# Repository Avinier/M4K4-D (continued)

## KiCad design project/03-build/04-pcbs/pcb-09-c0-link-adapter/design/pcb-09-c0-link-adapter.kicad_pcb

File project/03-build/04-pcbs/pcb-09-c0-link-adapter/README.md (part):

# PCB-09 — C0 link adapter

Pi-header board: 2 × RS-422 (THVD1451), audio pass-through and the enclosure-fan switch `J9-4`. **Rev A designed** ([D-092](../../decisions.md#d-092)): 77 × 22.7 × 1.6 mm, four layers, on the Pi header through a Samtec SSW-120-01-T-D socket and two M2.5 × 11 mm standoffs. **Rev B routed and CAD fitted on `pcb-09-revB`, not released** ([D-098](../../decisions.md#d-098)): 89 × 22.7 × 1.6 mm overall, adding the D-096 button/OFF and INA226 service interface. The #2813, Pi-image and populated bench gates below still apply; do not order either revision yet.

| | |
|---|---|
| Register | [04-pcbs board register](../README.md#board-register) |
| Project BOM | CH-084 in [BOM.csv](../../BOM.csv) |
| Location | Body, on the Pi header |
| Specification | [audiosystem.md §4](../../02-body/v1/research/audiosystem.md#4-audio-functions-on-the-shared-boards)<br>[D-042](../../decisions.md#d-042), [D-073](../../decisions.md#d-073), [D-074](../../decisions.md#d-074), [D-092](../../decisions.md#d-092), [D-098](../../decisions.md#d-098) |
| CAD placeholder | `_c0_link_adapter()` in [`body_v1_model.py`](../../02-body/v1/cad/body_v1_model.py) |
| CAD labels | `C0_LINK_ADAPTER_PCB09` |
| Final CAD | `Custom PCBs › PCB-09 C0 link adapter` in [makad-v1.step.py](../../final/v1/cad/makad-v1.step.py): rev-B KiCad STEP, standoffs, screws and five mated plugs ([pcb_integration.py](../../final/v1/cad/pcb_integration.py)); rev-B fit 8/8, mount 7/7 and integration PASS |

## Stages

See [workflow.md](../workflow.md) for what each stage involves and when it is done.

| Stage | Status | Revision / evidence | Date |
|---|---|---|---|
| 1. Design | **Rev B routed and CAD fitted; electrical release gates open** ([D-098](../../decisions.md#d-098)) | ERC 0; exported netlist audit PASS for 118 connected pins; Nightly DRC 0 violations / 0 unconnected / 0 parity; rev-B fit 8/8, mount 7/7, final integration PASS. `fab/revB` is a draft output, not an order release. | 2026-11-08 |
| 2. Procure | Waits for rev B and the design batch ([D-064](../../decisions.md#d-064)) | Do not order fab/revA | — |
| 3. Integrate | Rev B CAD replacement complete; physical acceptance open | [pcb_integration.py](../../final/v1/cad/pcb_integration.py), `check_pcb_integration.py`; J6 lead route to rear bay passes a 3 mm CAD reserve with 0.2 mm margin. J6 must be mated before tray installation. | 2026-11-08 |

### Rev B input — D-098

Preserve the rev A functions, socket, mounting and existing connector pinouts. Add accessible service access to **GPIO12 / header 32** for the qualified 0–3.3 V button-sense signal and **GPIO13 / header 33** for the M1 OFF command. The [D-098 amendment](../../decisions.md#d-098) assigns the INA226 to a local `i2c-gpio` bus: draft SDA on GPIO16 / header 36 and SCL on GPIO26 / header 37, plus Pi 3.3 V and GND. Physical pins 3/5 keep their rev A I²C1 routes to TP1/TP2 only. TP5 and TP1/TP2 are 1 mm probe pads, not harness terminations.

Rev B selects J6 as a top-entry GH6 on the +X extension. CAD checks its mated plug, a 3 mm lead corridor toward the rear buffer, and pre-mated tray insertion; add strain relief and pull-test the lead on the populated build. Keep the M1 ON pack-voltage node off this board: GPIO12 receives only the output of the measured high-impedance interface, with no back-power path into an unpowered Pi. Check GPIO13's inactive state through Pi reset, boot and halt, and any M1-to-GPIO13 injection with Pi power absent, before connecting OFF. ERC/DRC, six-net continuity/no-short checks and N1 are release gates. D-096's separate electrical HOLD still applies.

### Rev B routing study — 2026-11-08

The [rev B schematic](design/pcb-09-c0-link-adapter.kicad_sch) adds J6 (GH6: **1 3V3, 2 SDA, 3 SCL, 4 GND, 5 BTN_SENSE, 6 PWR_OFF**), R7 10 kΩ button pull-up to Pi 3V3, R8 2.2 kΩ button series, C5 100 nF optional/DNP, R9 1 kΩ OFF series, R10 100 kΩ OFF pull-down, and R11/R12 4.7 kΩ pull-ups for the software I²C bus. GPIO12/13 terminate at header pins 32/33; draft SDA/SCL terminate at pins 36/37. The connector nets are on the 3.3 V side; pack voltage and load current are absent. The received #2813 measurements still gate final values and buffer choice.

| Header pin | Rev B schematic net | Destination | Layout status |
|---|---|---|---|
| 3 / GPIO2 | I2C1_SDA | TP1 only, unchanged from rev A | Rev A route retained in rev B |
| 5 / GPIO3 | I2C1_SCL | TP2 only, unchanged from rev A | Rev A route retained in rev B |
| 32 / GPIO12 | BTN_GPIO12 | R8 → BTN_SENSE at J6.5 | Routed in rev B; DRC 0/0/0 |
| 33 / GPIO13 | OFF_GPIO13 | R9 → PWR_OFF at J6.6 | Routed in rev B; DRC 0/0/0 |
| 36 / GPIO16 | I2C_GPIO_SDA | R11 pull-up and J6.2 | Routed in rev B; DRC 0/0/0 |
| 37 / GPIO26 | I2C_GPIO_SCL | R12 pull-up and J6.3 | Routed in rev B; DRC 0/0/0 |

The draft rev B allocation has **15 functional GPIO** (rev A's 11 plus GPIO12/13/16/26) and keeps GPIO2/3 reserved for I²C1 service pads. Layout and CAD fit validate GPIO16/26 and a top-entry GH6 at the +X extension; electrical acceptance is pending.

An exploratory GH6 placement needed an extension at the bay's +X edge: the existing F.Cu courtyards occupy the top of the original bay. A geometric core-only probe of world X 66…78, Y 22.5…39, Z 106.25…108.25 found no intersecting robot solid. That probe did **not** validate the mated plug, cable exit, insertion sweep, mount or full board. Growing the +Y edge instead intersected the existing J9-1 mated plug and its reserve.

The manually routed exploratory I²C1 board failed Nightly DRC: **29 violations, 2 unconnected and 0 parity** ([study report](design/revB-routing-study-drc.json)). The SDA F.Cu L path crossed LRCLK near header pin 35; the proposed layer change landed on the existing 5 V via. The SCL B.Cu U path crossed BASE_TX and approached a ground socket pad. The GPIO12/13 In1 paths isolated ground socket pads 30/34; J6's +X placement also conflicted with nearby vias. D-098 therefore switches the INA226 to local GPIO I²C and forbids new In1 tracks. This report is historical evidence from the rejected route.

The amended rev B layout uses local rev A escape reroutes near header pins 32–38, preserves every rev A net and connector pinout, adds no signal track to In1, and passes Nightly DRC 0/0/0. The +X extension ends at world X 78 and steps its +Y edge back to Y 38.9 to clear the body frame. The rev B STEP passes `check_pcb09_fit.py` 8/8, `check_pcb09_mount.py` 7/7, and `check_pcb_integration.py` PASS. `fab/revB/` was exported only after that CAD fit and remains a draft until the bench gates close.

Current evidence: [DRC/parity](design/layout-drc.json), [rev B board STEP](cad/pcb-09-c0-link-adapter-revB.step), [fit report](../../final/v1/cad/check_pcb09_fit-revB-report.json), [mount report](../../final/v1/cad/check_pcb09_mount-revB-report.json), [final STEP integration report](../../final/v1/cad/pcb-integration-report.json), and [draft fabrication outputs](fab/revB/README.md). C5 is DNP and omitted from the assembly BOM/CPL. J6's plug must be mated before the tray slide; its 3 mm lead reserve clears to the rear buffer volume with 0.2 mm CAD margin.

## Inputs

Header audit started 2026-10-31. The electrical interface below is the **builder-agreed allocation baseline v0.2** ([D-073](../../decisions.md#d-073)); CR-02 and boot-safe audit closure remain open. The D-074 strip outline and all 40 socket pad positions have since been checked, and a review schematic and placement exist below. Socket selection, installed height, retention and populated fit were the remaining lesson-1 gaps; they are closed in the [input freeze](#input-freeze--2026-11-06-d-092) (D-092).

**Audio contract, inherited from PCB-05.** `J9-3` (audio, `W26` to the BO-067 audio hub) carries signals only: GPIO18 BCLK, GPIO19 LRCLK, GPIO20 SDI0, GPIO22 SDI1, GPIO21 SDO0, GPIO23 `AMP_SD`, the Pi's 3V3, two GND and one spare, and **no 5 V** ([D-067](../../decisions.md#d-067), PCB-05 2026-10-27; `CA-06` CR-01 accepted there). The retained pin order is **1 3V3, 2 LRCLK, 3 GND, 4 BCLK, 5 GND, 6 SDO0, 7 SDI1, 8 SDI0, 9 AMP_SD, 10 spare (5V_SENSE)**; W26 is wired 1:1 to the hub. The spare still reaches only an isolated test pad on PCB-09; the retired PCB-05 divider is not fitted or part of the current build.

**Set by other boards.** `J9-2` (base link, `W25` to PCB-10 `J10-2`) was set by [PCB-10](../pcb-10-c3-carrier/README.md#connectors-and-who-owns-each-pin-order) on 2026-10-27 and reordered at its layout on 2026-10-28 (the order its THVD1451's pins come in, so the pairs run straight). The pairs are named by direction so `W25` is wired 1:1: 1 GND, 2 `C0TX+` and 3 `C0TX−` (this board's driver `Y`/`Z`), 4 `C3TX−` and 5 `C3TX+` (this board's receiver `B`/`A`, with its 120 Ω termination), 6 spare. The `J9-1` head link may follow the same rule; that is this board's choice.

### Pi 5 header audit — 2026-10-31

**Lesson.** A GPIO has three separate properties: where it is on the connector, which peripheral it can carry, and what voltage it presents before software takes control. A correct UART pin can still send a break at boot; a correct fan pin can still turn the switch partly on if its bias is wrong. Covering all 40 contacts also makes PCB-09 responsible for access to reserved buses. Mechanical contact with a socket does not imply an electrical trace on the adapter.

**Result:** BCM-to-header mappings and proposed peripheral functions pass the paper check; the active owners do not overlap. **The complete boot-safe interface is not yet passed or frozen. CR-02 remains OPEN:** GPIO24 is the builder-selected, conflict-free fan pin; accepting the entire change still requires the outstanding evidence below. CR-01 remains accepted under D-067; this audit adds software implementation conditions rather than reopening that allocation. The builder accepted HA-02…04's recommended dispositions on 2026-10-31 (D-073), explicitly retaining CR-02 as open.

#### Evidence and authority

Read on 2026-10-31. RP-02 is read-only; build changes belong here and in [decisions.md](../../decisions.md); the selected dispositions are recorded as D-073. Source-code URLs use Raspberry Pi's `rpi-6.12.y` branch as an inspected reference, **not** evidence of the kernel installed on C0.

| Ref | Source | What was checked |
|---|---|---|
| H | Raspberry Pi [40-pin header documentation](https://www.raspberrypi.com/documentation/computers/raspberry-pi.html#gpio) and its [pin diagram](https://raw.githubusercontent.com/raspberrypi/documentation/master/documentation/asciidoc/computers/raspberry-pi/images/GPIO-Pinout-Diagram-2.png) | All 40 physical positions, supply contacts, GPIO0/1 reservation; 3.3 V GPIO, no 5 V tolerance. The shared diagram's older peripheral labels are not the Pi 5 mux authority |
| R | [RP1 peripherals datasheet](https://datasheets.raspberrypi.com/rp1/rp1-peripherals.pdf), §3.1 Table 4, GPIO CTRL and PADS Table 21 | UART/I²S mux, NULL reset function, output disabled and input buffer disabled at reset |
| P | Raspberry Pi engineer clarification, [Pi5 GPIO Reset Defaults](https://forums.raspberrypi.com/viewtopic.php?t=366826), 2024-03-04…06 | GPIO0–8 pull up; GPIO9–27 pull down. Table 21 only says “varies”; this clarification supplies the per-pin bias and corrects the initial “inputs” description |
| T | TI [THVD1451, SLLSEY3E](https://www.ti.com/lit/ds/symlink/thvd1451.pdf), §§7.3, 7.5, 7.7, 9.1 | 3.0–5.5 V operation, logic thresholds, receiver swing, 3 mA maximum no-load current; always-enabled driver and receiver |
| U | Official [uart0-pi5](https://raw.githubusercontent.com/raspberrypi/linux/rpi-6.12.y/arch/arm/boot/dts/overlays/uart0-pi5-overlay.dts), [uart2-pi5](https://raw.githubusercontent.com/raspberrypi/linux/rpi-6.12.y/arch/arm/boot/dts/overlays/uart2-pi5-overlay.dts), [rp1.dtsi](https://raw.githubusercontent.com/raspberrypi/linux/rpi-6.12.y/arch/arm64/boot/dts/broadcom/rp1.dtsi) and [overlay reference](https://raw.githubusercontent.com/raspberrypi/linux/rpi-6.12.y/arch/arm/boot/dts/overlays/README) | UART pin groups and optional flow-control claims; default I²S group stops at GPIO21 |
| F | Official [gpio-fan overlay](https://raw.githubusercontent.com/raspberrypi/linux/rpi-6.12.y/arch/arm/boot/dts/overlays/gpio-fan-overlay.dts) and [driver](https://raw.githubusercontent.com/raspberrypi/linux/rpi-6.12.y/drivers/hwmon/gpio-fan.c) | One active-high control pin; temperature and hysteresis parameters; probe preserves the observed GPIO level, shutdown drives off |
| B | Official [UART configuration](https://www.raspberrypi.com/documentation/computers/configuration.html#configuring-uarts) and [BOOT_UART](https://www.raspberrypi.com/documentation/computers/raspberry-pi.html#BOOT_UART) | Pi 5 debug UART is normally UART10 on the separate debug connector; configuration can change the primary UART, so silence on GPIO14 must be checked on the installed image |
| C | RP-02 [CA-06](../../../02-prototypes/RP-02-electrical/compute-control-architecture.md#ca-06--pi-gpio-allocation-reserves-independent-transports), [D-042](../../decisions.md#d-042), [D-043](../../decisions.md#d-043), [D-067](../../decisions.md#d-067), PCB-05/PCB-10 READMEs linked above | Existing allocations, fan circuit, selected 3010 fan, connector contracts and audio power ownership |

#### 40-row header interface (rev A baseline with rev B service additions)

Directions are relative to the Pi. `N↑`/`N↓` mean **NULL function, output disabled, input buffer disabled**, with the indicated weak pull at RP1 reset (R/P); they do not promise an unchanged state throughout firmware, Linux or a warm reboot. Voltages are nominal signal/rail domains, not absolute maximum ratings. `NC` means a socket contact with **no trace, via, test pad or other load on PCB-09**, apart from its own land. Reserved contacts remain reserved even when NC. Supply rows are shared rail contacts, not competing GPIO owners.

| Physical pin | BCM GPIO | PCB-09 net / disposition | Owner / authority | Direction | RP1 reset / external bias | Voltage |
|---|---|---|---|---|---|---|
| 1 | — | +3V3_PI | Pi supply → PCB-09 + audio hub | Power in | Rail sequencing | 3.3 V |
| 2 | — | +5V_PI → fan only | D-042 / D-043 | Power in | May remain powered at halt | 5 V |
| 3 | 2 | I2C1_SDA → labelled SDA service pad | CA-06 / D-073 housekeeping | Bidirectional | N↑; Pi has fixed pull-up | 3.3 V |
| 4 | — | +5V_PI, same rail as pin 2 | D-042 / D-043 | Power in | May remain powered at halt | 5 V |
| 5 | 3 | I2C1_SCL → labelled SCL service pad | CA-06 / D-073 housekeeping | Bidirectional | N↑; Pi has fixed pull-up | 3.3 V |
| 6 | — | GND | Common return | Return | GND | 0 V |
| 7 | 4 | BASE_TX → base THVD1451 D | CA-06 UART2 | Out | N↑; 4.7 kΩ to 3V3 (D-073) | 3.3 V |
| 8 | 14 | HEAD_TX → head THVD1451 D | CA-06 UART0 | Out | N↓; 4.7 kΩ to 3V3 (D-073) | 3.3 V |
| 9 | — | GND | Common return | Return | GND | 0 V |
| 10 | 15 | HEAD_RX ← head THVD1451 R | CA-06 UART0 | In | N↓; R drives after VCC valid | 3.3 V |
| 11 | 17 | NC; UART0 RTS prohibited | PCB-09 unused | — | N↓ | 3.3 V |
| 12 | 18 | BCLK → J9-3.4 | CA-06 / D-067 I²S0 | Out | N↓ | 3.3 V |
| 13 | 27 | NC | PCB-09 unused | — | N↓ | 3.3 V |
| 14 | — | GND | Common return | Return | GND | 0 V |
| 15 | 22 | SDI1 ← J9-3.7 | CR-01 / D-067 I²S0 | In | N↓; converter powered by Pi | 3.3 V |
| 16 | 23 | AMP_SD → J9-3.9 | CR-01 / D-067 GPIO | Out | N↓; verify amp/hub bias on the build | 3.3 V |
| 17 | — | +3V3_PI, same rail as pin 1 | Pi supply → PCB-09 + audio hub | Power in | Rail sequencing | 3.3 V |
| 18 | 24 | FAN_EN → 100 Ω → MOSFET gate | D-042 / D-073; CR-02 open | Out | N↓; 100 kΩ gate–source | 3.3 V |
| 19 | 10 | NC; SPI0 MOSI reserved | CA-06 SPI/service | — | N↓ | 3.3 V |
| 20 | — | GND | Common return | Return | GND | 0 V |
| 21 | 9 | NC; SPI0 MISO reserved | CA-06 SPI/service | — | N↓ | 3.3 V |
| 22 | 25 | NC | PCB-09 unused | — | N↓ | 3.3 V |
| 23 | 11 | NC; SPI0 SCLK reserved | CA-06 SPI/service | — | N↓ | 3.3 V |
| 24 | 8 | NC; SPI0 CE0 reserved | CA-06 SPI/service | — | N↑ | 3.3 V |
| 25 | — | GND | Common return | Return | GND | 0 V |
| 26 | 7 | NC; SPI0 CE1 / UART2 RTS alternatives | PCB-09 unused | — | N↑ | 3.3 V |
| 27 | 0 | NC; ID_SD only | Pi HAT-ID reservation | — | N↑ | 3.3 V |
| 28 | 1 | NC; ID_SC only | Pi HAT-ID reservation | — | N↑ | 3.3 V |
| 29 | 5 | BASE_RX ← base THVD1451 R | CA-06 UART2 | In | N↑; R drives after VCC valid | 3.3 V |
| 30 | — | GND | Common return | Return | GND | 0 V |
| 31 | 6 | NC; UART2 CTS prohibited | PCB-09 unused | — | N↑ | 3.3 V |
| 32 | 12 | BTN_GPIO12 via R8 from J6.5 BTN_SENSE | D-098 button sense | In | N↓; R7 pulls sense to Pi 3V3 | 3.3 V |
| 33 | 13 | OFF_GPIO13 via R9 to J6.6 PWR_OFF | D-098 M1 OFF | Out | N↓; R10 pulls PWR_OFF low | 3.3 V |
| 34 | — | GND | Common return | Return | GND | 0 V |
| 35 | 19 | LRCLK → J9-3.2 | CA-06 / D-067 I²S0 | Out | N↓ | 3.3 V |
| 36 | 16 | I2C_GPIO_SDA → J6.2; R11 pull-up | D-098 software I²C; UART0 CTS prohibited | Bidirectional | N↓; 4.7 kΩ to Pi 3V3 | 3.3 V |
| 37 | 26 | I2C_GPIO_SCL → J6.3; R12 pull-up | D-098 software I²C | Bidirectional | N↓; 4.7 kΩ to Pi 3V3 | 3.3 V |
| 38 | 20 | SDI0 ← J9-3.8 | CA-06 / D-067 I²S0 | In | N↓; converter powered by Pi | 3.3 V |
| 39 | — | GND | Common return | Return | GND | 0 V |
| 40 | 21 | SDO0 → J9-3.6 | CA-06 / D-067 I²S0 | Out | N↓ | 3.3 V |

**Rev B count:** 15 functional GPIO (including FAN_EN with CR-02 open), 2 reserved I²C1 GPIO exposed only on service pads, 11 other GPIO contacts, 4 supply contacts and 8 grounds = 40. GPIO0/1 have no adapter EEPROM or test points. Both contacts of each supply rail join that rail; all eight grounds join the common plane. J9-3.1 gets +3V3_PI; J9-3.3/.5 get GND. J9-3.10 goes **only to an isolated 5V_SENSE test pad**, never to a Pi GPIO or either supply. Its name does not make it a 5 V power connection.

#### Function selection and software ownership

Table 4 (R) confirms UART0 on GPIO14/15 at **a4**, UART2 on GPIO4/5 at **a2**, and I²S0 BCLK/WS/SDI0/SDO0/SDI1 on GPIO18/19/20/21/22 at **a2**. GPIO23 and GPIO24 use plain GPIO outputs (RIO path), never I²S. GPIO23's a2 is SDO1; GPIO24's a2 is SDI2, so enabling additional audio lanes indiscriminately would collide with both control signals.

| Consumer | Allowed GPIO claim | Condition / finding |
|---|---|---|
| `uart0-pi5` | 14, 15 | Use the Pi 5 overlay explicitly. No `ctsrts` or `rs485`: those also claim 16/17. Full-duplex THVD1451 needs no RTS control |
| `uart2-pi5` | 4, 5 | No `ctsrts` or `rs485`: those also claim 6/7 |
| Audio sound-card overlay | 18, 19, 20, 21, 22 only | **Not yet supplied or compiled.** The inspected `rp1_i2s0_18_21` group omits SDI1. Define/select a five-pin I²S0 group; keep GPIO23/24 out of it. Bind one shared clock interface with four capture channels on two stereo lanes and two-channel playback; enabling `i2s` alone is not a sound-card implementation |
| Amp control | 23 only | Start low; assert only after valid playback clocks/data; lower before stopping clocks and at orderly shutdown. One software owner; do not combine a permanent GPIO hog with a driver that also requests it |
| `gpio-fan` | 24 only | Proposed `dtoverlay=gpio-fan,gpiopin=24,temp=60000,hyst=5000`: 60 °C on / 55 °C off. Explicit pin required: the default is GPIO12. Temperatures remain bench starting points |
| I²C1 | 2, 3 reserved; SDA/SCL/GND service pads (D-073) | No additional pull-ups, attached consumer or bus cable. Keep the controller disabled until a consumer is deliberately configured |
| Button sense and M1 OFF (rev B) | 12 input, 13 output (D-098) | Button sense must be 0–3.3 V after a qualified rear buffer; verify GPIO13 stays inactive through boot, reboot and halt. J6 termination and cable CAD fit pass; electrical checks remain |
| `i2c-gpio` INA226 (rev B) | 16 SDA, 26 SCL | R11/R12 pull each line to Pi 3V3; keep UART0 flow control off and test INA226 at 0x40 on the actual Pi image |
| SPI0 | None | Reservation preserved; no adapter traces or access. SPI0's usual second CS is GPIO7, outside CA-06's 8–11 shorthand; leave SPI disabled unless deliberately configured |

**Console check is a release condition.** Pi 5 normally sends debug output through UART10, not GPIO14/15 (B); that is not proof that every EEPROM/image configuration is silent. Require EEPROM `BOOT_UART=0`, disable firmware debug output (`uart_2ndstage`), remove any kernel `console=`/`earlycon` targeting either link (including aliases), and disable serial getty/debug applications on both resolved ports. Preserve CA-06's stable udev names and boot mux self-test. Capture the installed EEPROM settings, `config.txt`, `cmdline.txt`, resolved aliases and enabled services; scope HEAD_TX through cold boot, warm reboot and shutdown. `enable_uart=1` alone is not the pin-ownership proof.

#### Boot/reset findings and selected circuit remedies

1. **FAN_EN: correct default, incorrect “beats any pull-up” premise.** GPIO24 is reset NULL/pulled down, so its internal pull and D-042's 100 kΩ gate-to-source resistor agree. Retain the 100 Ω series resistor, gate pull-down at the MOSFET, common source ground, flyback Schottky (cathode to FAN+, anode to FAN−), and local 10 µF + high-frequency bypass. A 100 kΩ pull-down does not dominate a tens-of-kΩ pull-up: even an illustrative 50 kΩ pull-up gives about 2.2 V at the gate. Thus no overlay/firmware may enable a pull-up or other function on GPIO24. With only 100 kΩ present, require the selected MOSFET's worst-case gate leakage plus board leakage to keep VGS below its off limit. Confirm gate voltage and fan inactivity on real cold boot/reset; an output driven high by a hung kernel is not corrected by a pull-down. This is a reset-off switch, not an independent thermal failsafe.
2. **UART TX: head reset is a break, not an unspecified floating signal.** GPIO14 defaults pulled down; THVD1451 forwards D continuously. GPIO4 defaults pulled up and is nominally idle-high. Add **4.7 kΩ from each D/TX to the same Pi 3V3 rail** (D-073): both links then have a deliberate idle-high bias before the UART owns them. TI specifies up to 6.2 µA D input leakage; include it and the opposing RP1 pull in the high-level calculation, against TI's 2.0 V VIH. A 100 kΩ pull-up is unsuitable against the head pin's pull-down. As a cross-check only, the [CM5 RP1 GPIO table](https://pip-assets.raspberrypi.com/categories/944-raspberry-pi-compute-module-5/documents/RP-008180-DS-7-cm5-datasheet.pdf?disposition=inline) gives a 35 kΩ minimum pull-down: 3.0 V × 35/(35+4.747) − 6.2 µA × (35 kΩ ∥ 4.747 kΩ) ≈ **2.62 V** with a +1% pull-up. This is a same-controller comparison, not a Pi 5 board-specific guaranteed limit; confirm the Pi 5 bound or measure with margin before sign-off. Low-state pull-up load at 3.3 V is about 0.70 mA. Pull-ups cannot suppress actively transmitted boot text or guarantee clean signalling while VCC ramps. C2/C3 must reject framing errors, breaks, stale sessions and invalid commands before arming; verify recovery after these events.
3. **AMP_SD: reset bias agrees with off.** GPIO23's pull-down reinforces PCB-05's external 100 kΩ and MAX98357A's internal pull-down, through the existing 2.2 kΩ series resistor (D-067). No I²S group may take GPIO23. That remote pull-down defines off if W26 is unplugged. PCB-05 owns the unpowered-amp SD_MODE injection mitigation; its accepted 2.2 kΩ circuit remains the contract. A warm reboot need not instantly restore RP1 reset defaults: test amp mute ordering rather than assuming it.
4. **Audio inputs and outputs.** SDI0/SDI1 come from converters supplied from the Pi's own 3V3, with a passive filtered mic rail; no independent 5 V receiver drives a Pi input. BCLK/LRCLK/SDO0 are outputs, normally held low by reset bias while the amp is off. Retain PCB-05's clock damping and verify clock edges and rail sequencing with the real W26. Shared supply origin does not by itself prove transient sequencing during a fast shutdown; scope the filtered rail and SDI lines at bring-up.

#### Voltage and rail budget

Both THVD1451 VCC pins and TX pull-ups must use **+3V3_PI, never +5V_PI**. TI's receiver high is referenced to VCC; with VCC = 3.3 V its specified VOH ≥ VCC − 0.4 V at −8 mA is compatible with 3.3 V Pi logic. A 5 V supply would expose RX to a 5 V-class output. Put 100 nF at each VCC/GND pair. Each local receiver A/B pair gets 120 Ω; no extra termination across this board's Y/Z driver pair (the far receiver terminates it). TI's open/short/idle receiver fail-safe does not fix a low or noisy driver D input. Keep the transceiver selection open until its footprint and alternatives are reviewed; a substitute needs its own bias/power check.

| Header rail | Incremental loads | Paper allowance / remaining evidence |
|---|---|---|
| 3V3 | Two THVD1451, both continuously driving remote 120 Ω loads | No-load maximum **2 × 3 = 6 mA**. Termination current is additional: a deliberately conservative 3.3 V/120 Ω ceiling per driver gives **55 mA** total load current; about **61 mA** including quiescent, before dynamic/cable-capacitance current |
| 3V3 | Four INMP441 modules via J9-3.1, INA226 via J6.1 | About **5.6 mA** for the four mics at 1.4 mA each and **0.3 mA** for the INA226; verify the bought modules and actual current. The retired PCB-05's 15 mA allowance is no longer the load model |
| 3V3 | TX, I²C and button pull-ups; AMP_SD and switching activity | Up to about **1.4 mA** for both TX pull-ups held low, **1.4 mA** for both 4.7 kΩ I²C pull-ups held low, and **0.33 mA** for the 10 kΩ button pull-up held low, plus amp-control bias and dynamic current; retain **80 mA provisional normal-operation allocation** for the sub-branch and measure under link/audio load. This is not a short-circuit or inrush rating |
| 5V | D-043's purchased 3010 fan via J9-4.1, local capacitor charging | Running, startup and locked-rotor currents **unknown**. No defensible numerical total or rail-margin pass yet; measure the actual fan, not the superseded 4010 listing |

3V3 fault demand is separate: TI lists driver short-circuit current magnitude up to 250 mA per device; two shorted outputs could dominate the 80 mA normal allowance. Check supply droop/current limiting and fault behaviour before release. The Pi header rails are supply outputs here; there is no external rail tied in through W25/W26/W41. Size the 5 V path, ground return, MOSFET at its **2.5/3.3 V gate drive**, diode, connector and protection from measured fan startup/stall and capacitor inrush. `VGS(th)` is not an on-resistance specification. The full Pi + USB + Active Cooler + adapter budget remains under the compute branch; available fan margin cannot be inferred from a “5 A supply” label alone. Keep fan current loops away from mic/audio returns.

#### Findings and dispositions (D-073)

| ID | Finding | Proposed disposition / closure |
|---|---|---|
| HA-01 | All assigned BCM/physical mappings and mux functions pass; no active pin collision | Allocation baseline v0.2 agreed by the builder under D-073, including HA-02…04 below. Boot-safe audit closure remains open; physical socket mirroring is the next step |
| HA-02 | CA-06's reserved I²C1 is inaccessible under the full socket; no v1 consumer/harness is identified in the reviewed build specs | **Selected 2026-10-31:** preserve access with labelled SDA/SCL/GND service pads on PCB-09; no additional pull-ups (Pi already has them), bus cable or consumer implied. Pins 3/5 are routed to their respective service pads; the CA-06 reservation remains |
| HA-03 | UART0 reset sends a break; base TX relies on a weak default pull | **Selected 2026-10-31:** fit two 4.7 kΩ TX pull-ups to Pi 3V3. Check Pi-specific worst-case bias and scope startup before release; framing/session checks stay mandatory |
| HA-04 / CR-02 | GPIO24 is suitable and has the correct reset pull. The fan circuit/current and deployed software are not fully verified | **Selected 2026-10-31:** retain GPIO24 and the D-042 100 kΩ pull-down, with the documented mux restriction. CR-02 stays OPEN until boot/overlay and fan-current checks pass; do not claim full audit pass or schematic implementation |
| HA-05 | Stock I²S group does not include GPIO22; a broad lane group could steal GPIO23/24 | Custom audio overlay required; compile/apply to the exact target DTB and inspect merged pinctrl/claims, then prove four-channel capture + playback and independent AMP_SD/FAN_EN |
| HA-06 | Pi 5 normally uses separate debug UART, but the installed image/EEPROM was not inspected | Record console/getty/alias configuration and scope both TX lines through cold boot, reboot and halt; prove no boot text on either link |
| HA-07 | Fan current and complete rail margin not established | Measure D-043 fan run/start/stall, verify switch ratings, inrush, rail droop and thermal/noise conditions. Normal 3V3 estimate is not a measured rail budget |
| HA-08 | J9-3 spare must not silently acquire a GPIO | Isolated test pad only; no GPIO claim without CR-03. J9-2.6 remains spare/NC; J9-1 order still to be chosen with its far-end contract |

**Builder disposition recorded:** “Use all three recommendations” (2026-10-31), [D-073](../../decisions.md#d-073). D-042's CR-02 cross-reference records that it is still open. Historical RP-02 is unchanged. The next design step is the CAD envelope and socket-orientation check; implement the selected service pads and TX bias in the schematic afterwards. Evidence needing the deployed Pi or real fan remains an integration/release gate.

### Mechanical inputs and socket orientation — 2026-10-31

**Lesson.** A connector's plastic body is only part of its footprint. Copper pads need an edge margin, solder tails occupy the other face, and courtyards reserve assembly space around neighbouring parts. A board can clear the robot in CAD while still leaving pads outside its outline. This survey checks those separately.

**CAD brief.** Inspect the current PCB-09 placeholder, its mating Pi header and nearby body/chassis parts in world millimetres (+X forward, +Y robot-left, +Z up). Keep the accepted electrical map and connector pin orders. Measure the board and screen the stock socket/SOIC/GH footprints. The initial survey tested the strip extension without changing geometry; the builder then approved it and it is applied in the final assembly under [D-074](../../decisions.md#d-074). Output: the reusable [input survey](../../final/v1/cad/check_pcb09_inputs.py) and its [measurement report](mechanical-audit.json). The final assembly entry is the geometry authority; subsystem sources stay unchanged.

**Run performed.** Built `chassis_v1_reference()` and `build_body_assembly()`, applied the current droid edits with `strict=False`, and intersected the actual shapes with board/face probes. Read the nightly library's socket, SOIC-8 and GH lands/courtyards. The script checks all 40 numbered pad centres and includes an intentionally wrong row reflection that fails on all 20 even pins. This is a static packaging and land-pattern screen, **not KiCad DRC, an insertion sweep or a final board fit check**. The head assembly was not built.

From the repository root:

```sh
rtk proxy env MAKAD_RELIEF_SERIAL=1 PYTHONPATH=project/03-build/03-head/v1/cad:project/03-build/02-body/v1/cad /Users/avinier/.codex/runtimes/text-to-cad/0.4.28/venv/bin/python project/03-build/final/v1/cad/check_pcb09_inputs.py --output project/03-build/04-pcbs/pcb-09-c0-link-adapter/mechanical-audit.json
```

#### Actual board outline and neighbourhood

The D-074 core is **1.6 mm**, at **Z 106.4…108.0**. It is the union of these three XY rectangles, not a 70.7 × 22.7 mm rectangle. Its volume is **1,299.344 mm³** (area 812.09 mm²), up 97.68 mm³ from the initial survey, and it remains one solid.

| Region | World X | World Y | Size XY |
|---|---|---|---|
| Header strip (D-074) | −4.7…36.0 | 16.3…22.4 | 40.7 × 6.1 |
| Bridge | 36.0…47.1 | 16.3…22.5 | 11.1 × 6.2 |
| Wide connector area | 36.0…66.0 | 22.5…39.0 | 30.0 × 16.5 |

Both the original core and the applied D-074 core have **zero intersecting external solids or reserves** in this static body/chassis check. This does not approve the populated board or its assembly path.

| Face / region probed | Nearest intersecting part or reserve in the probe | Consequence |
|---|---|---|
| Above strip, Z 108.001…128 | Yaw FFC cassette starts at Z 120.0; rolling-loop reserve at 121.35 | 12.0 mm geometric space above the core to the cassette in this column; leave assembly/tolerance margin. Socket solder tails and their copper still restrict placement |
| Below strip, Z 96.4…106.399 | Pi header tips at Z 104.045 | **2.355 mm** from pin tips to adapter underside. This is not a socket body height or a proved engagement length |
| Above wide area | PCB-05 +Y lead reserve starts at Z 115.6 over X 45…66, Y 22.5…28; fan lead at Z 118 over X 36…39, Y 33…39; frame at Z 126 | The lead reserve is only **7.6 mm** above the board face. J9-2's modelled header + plug reaches Z 115.4, leaving 0.2 mm vertically to that reserve. Route the leads deliberately; a body-only clearance is not a harness pass |
| Below wide area, Z 96.4…106.399 | No intersecting external solid/reserve in the 10 mm-deep column | Candidate space for underside circuitry. Initially keep parts within the old reserve's Z ≥ 104 floor (2.4 mm below the board), then check real parts, tails and service access |

These are spatially bounded probe results, not uniform allowable component heights. The Pi and cooler were intersected as geometry rather than treating their complete bounding boxes as solid obstacles. Old comments about 0.1 mm to the former XC330 position and the unshifted strip are not the current envelope authority.

#### Mating grid and socket numbering

The vendor Pi header is centred at approximately **(21.2, 19.331690)**. Its two rows are **Y 18.061690 and 20.601690**, pitch 2.54 mm, with 20 positions from **X −2.93 to 45.33**. Numbering follows the official Pi top-view diagram (H): pin 1 is the inner (−Y) row at the end away from USB/Ethernet (−X).

| Header pin | World XY | Sanity check |
|---|---|---|
| 1 | (−2.93, 18.061690) | 3V3, inner row |
| 2 | (−2.93, 20.601690) | 5 V, outer row |
| 39 | (45.33, 18.061690) | GND, inner row |
| 40 | (45.33, 20.601690) | GPIO21, outer row |

The socket mounts on the **underside** of PCB-09. The stock `PinSocket_2x20_P2.54mm_Vertical` library has pad 1 at (0, 0), pad 2 at (−2.54, 0), and pad 3 at (0, 2.54). For those **unplaced library coordinates**, the intended numbered mating map is:

```text
world X = −2.93 + library y
world Y = 18.061690 − library x
```

This specifies correspondence, not a KiCad rotation command. When the footprint is put on B.Cu, verify the actual placed pad centres against the report's 40-entry map; a bottom-side flip and an extra hand mirror must not both be applied. The script deliberately catches the wrong row reflection. Before power, continuity-check pins 1/2/6 and all assigned signals from the actual mating contacts to their destinations; verify the purchased socket's pin-1 drawing and the printed square-pad mark. No final physical footprint placement has yet been made.

#### Mechanical findings and dispositions

| ID | Evidence / gap | Disposition proposed for the next step |
|---|---|---|
| ME-01 | Stock socket pads are Ø1.7 mm. **Pins 2, 4, …, 32** extended past the original strip edge: outer copper reaches Y 21.451690 against edge 20.9. With the fab-neutral 0.3 mm edge gap, the minimum edge is **Y 21.751690** | **Closed by D-074, 2026-10-31:** builder approved and the final assembly now extends only the strip's +Y edge to 22.4 mm (width 4.6 → 6.1 mm), preserving bridge, wide area and core Z. All 40 stock pad envelopes pass the 0.3 mm screen; the current core has no static clash. The planted original outline still fails on 16 pads |
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
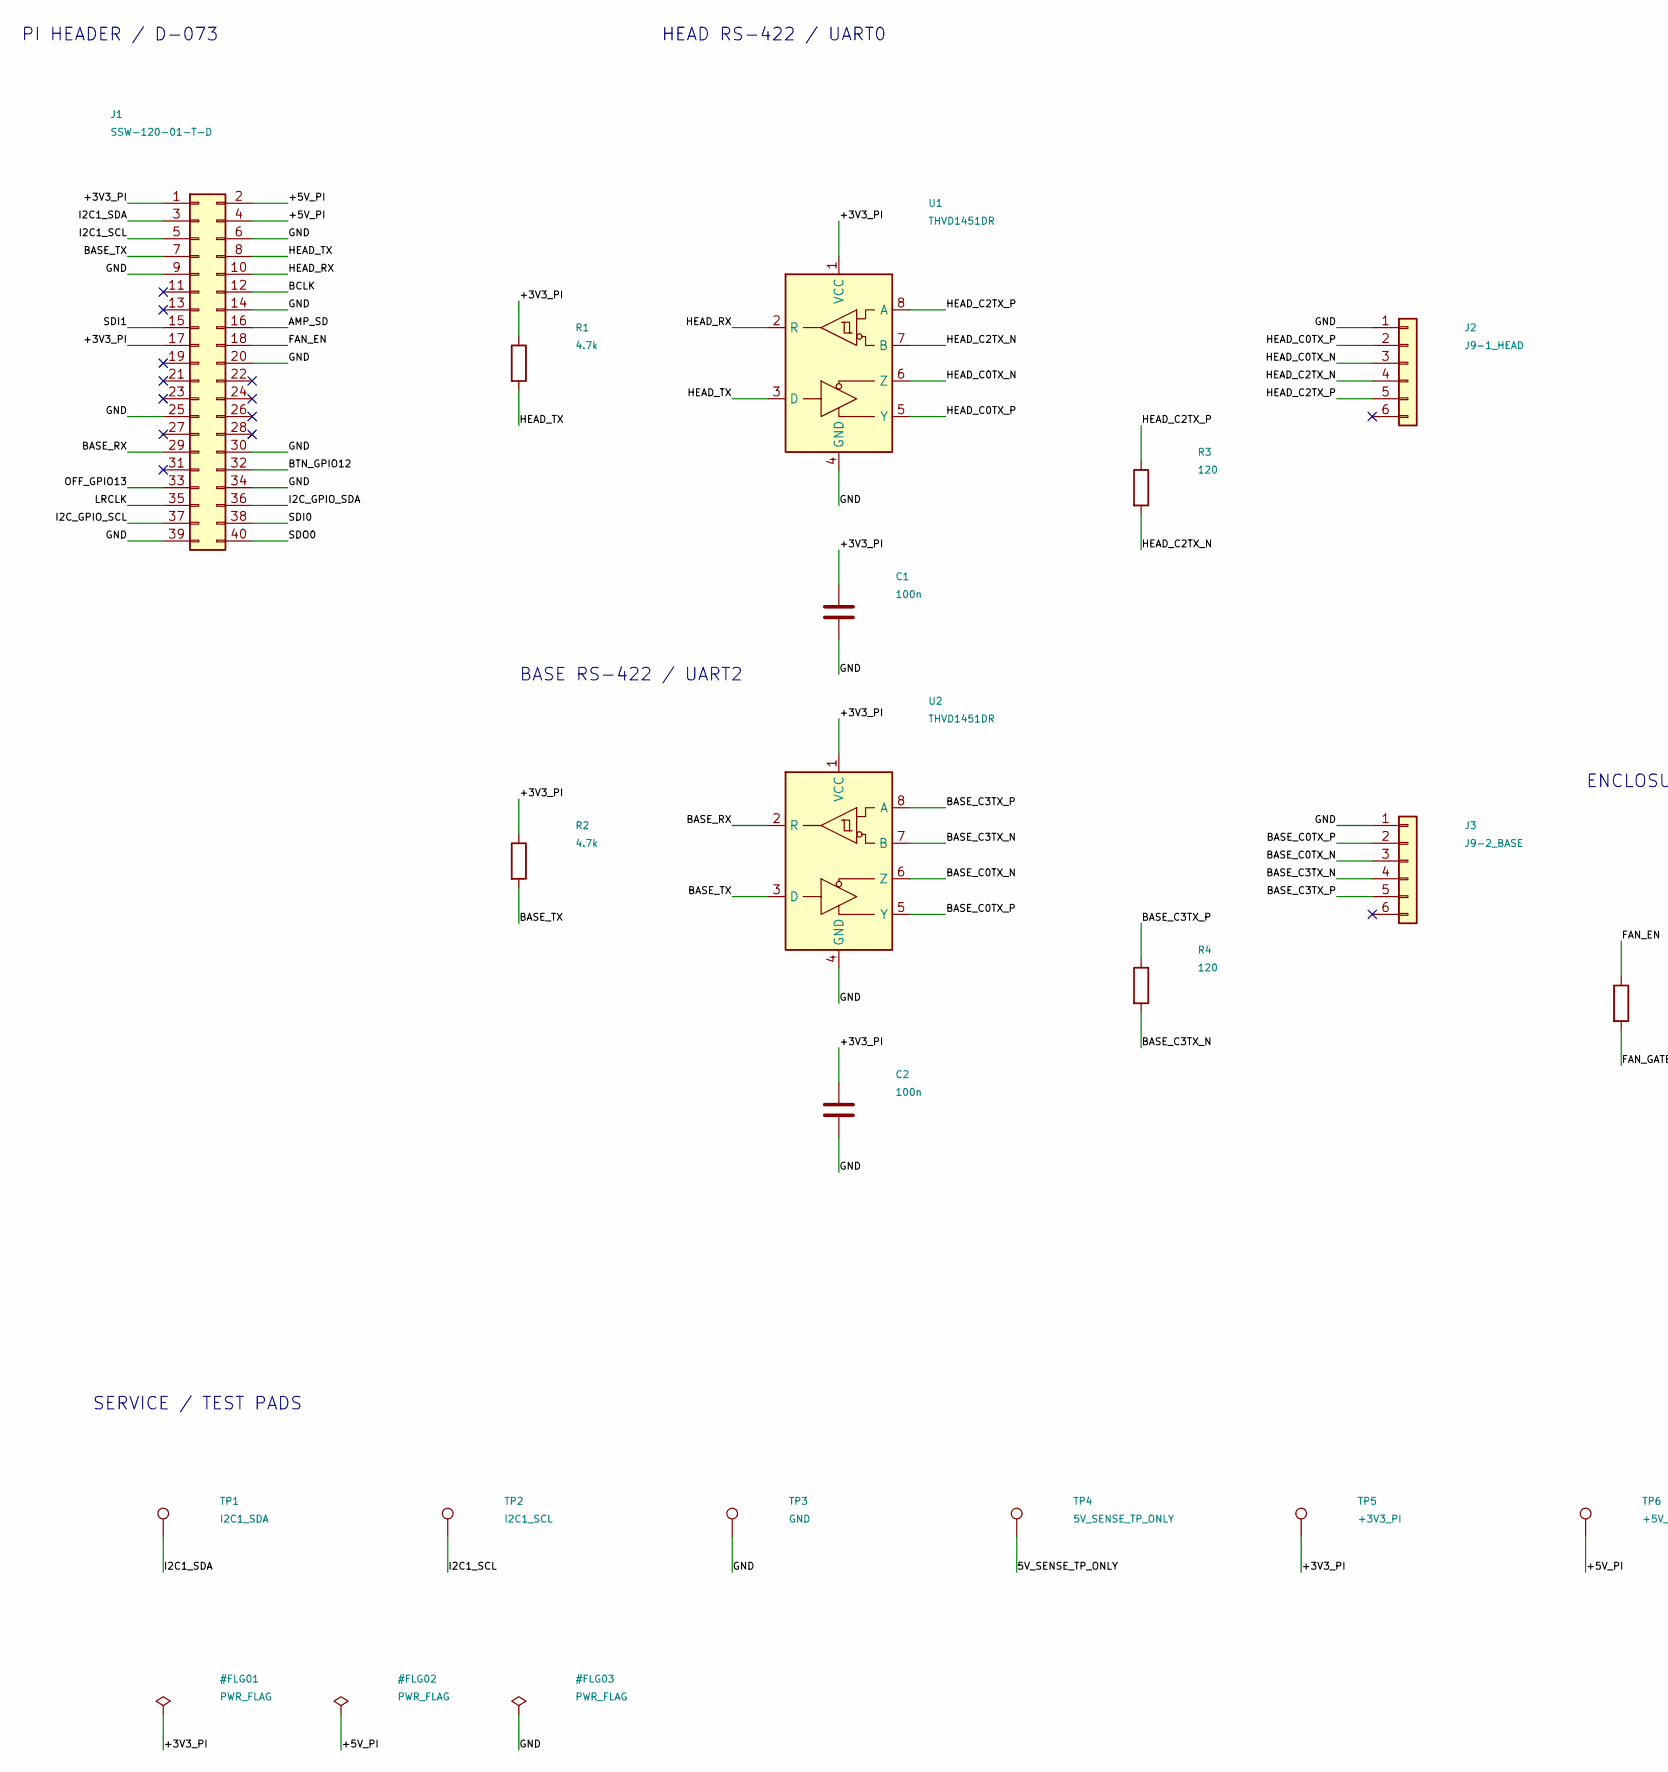
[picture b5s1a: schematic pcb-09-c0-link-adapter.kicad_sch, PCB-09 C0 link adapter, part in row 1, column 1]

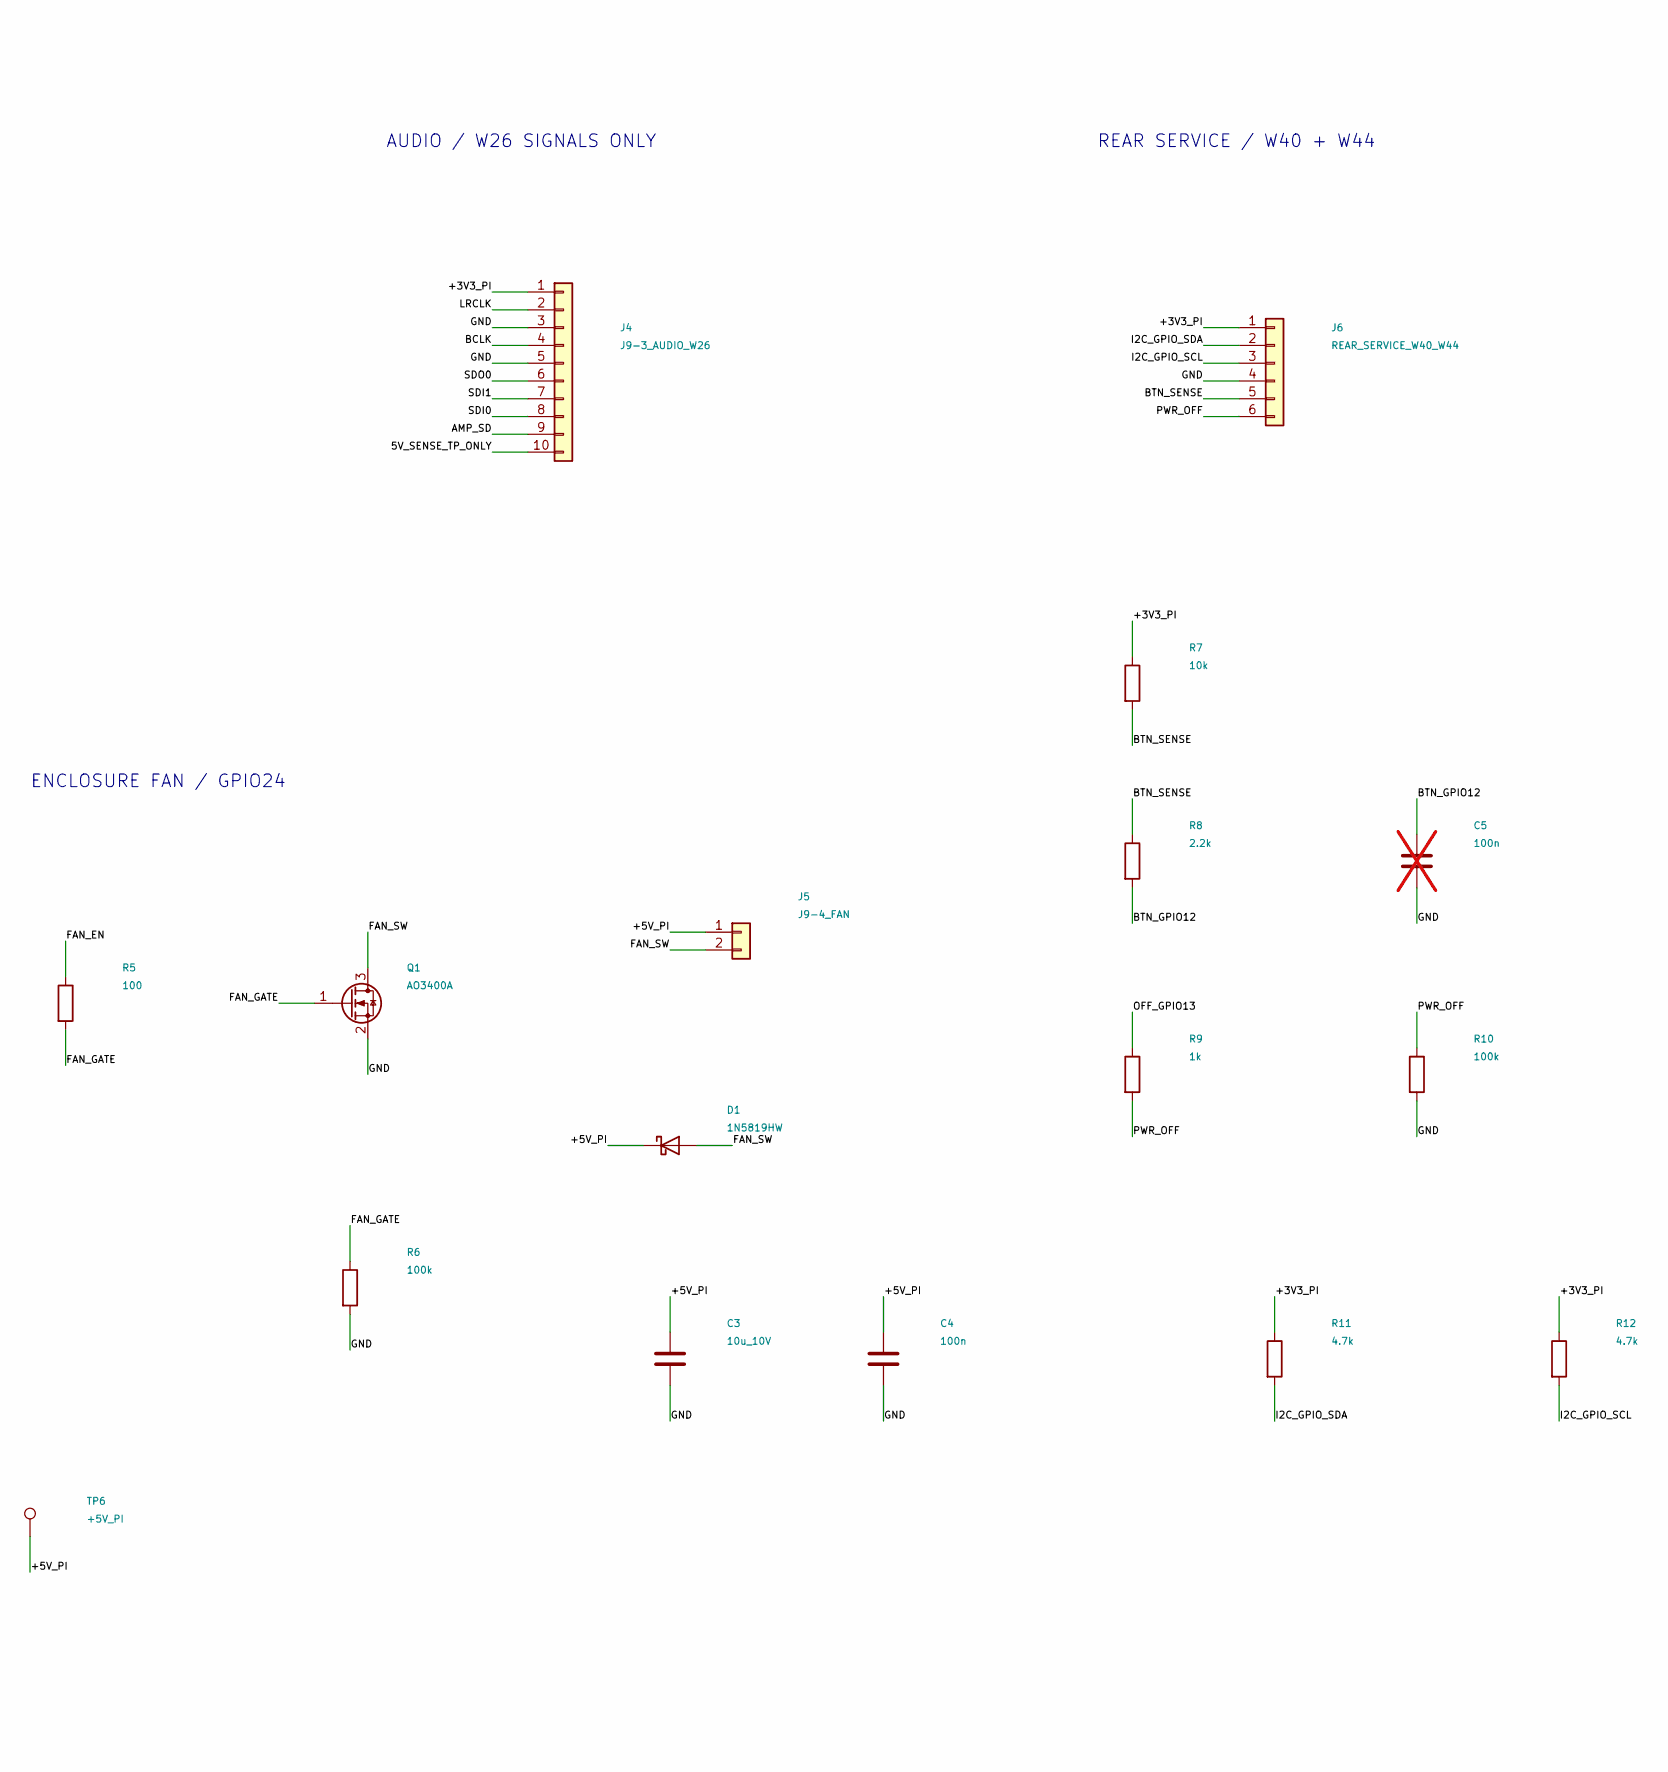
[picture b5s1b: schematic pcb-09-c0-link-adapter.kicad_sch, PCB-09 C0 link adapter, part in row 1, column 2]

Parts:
C1, C2, C4: 100n; C_0603_1608Metric
C3: 10u_10V; C_0805_2012Metric
C5: 100n; C_0603_1608Metric; not fitted
D1: 1N5819HW; D_SOD-123
J1: SSW-120-01-T-D; PinSocket_2x20_P2.54mm_Vertical
J2: J9-1_HEAD; JST_GH_SM06B-GHS-TB_1x06-1MP_P1.25mm_Horizontal
J3: J9-2_BASE; JST_GH_BM06B-GHS-TBT_1x06-1MP_P1.25mm_Vertical
J4: J9-3_AUDIO_W26; JST_GH_BM10B-GHS-TBT_1x10-1MP_P1.25mm_Vertical
J5: J9-4_FAN; JST_GH_BM02B-GHS-TBT_1x02-1MP_P1.25mm_Vertical
J6: REAR_SERVICE_W40_W44; JST_GH_BM06B-GHS-TBT_1x06-1MP_P1.25mm_Vertical
Q1: AO3400A; SOT-23
R1, R2, R11, R12: 4.7k; R_0603_1608Metric
R3, R4: 120; R_0603_1608Metric
R5: 100; R_0603_1608Metric
R6, R10: 100k; R_0603_1608Metric
R7: 10k; R_0603_1608Metric
R8: 2.2k; R_0603_1608Metric
R9: 1k; R_0603_1608Metric
TP1: I2C1_SDA; TestPoint_Pad_D1.0mm
TP2: I2C1_SCL; TestPoint_Pad_D1.0mm
TP3: GND; TestPoint_Pad_D1.0mm
TP4: 5V_SENSE_TP_ONLY; TestPoint_Pad_D1.0mm
TP5: +3V3_PI; TestPoint_Pad_D1.0mm
TP6: +5V_PI; TestPoint_Pad_D1.0mm
U1, U2: THVD1451DR; SOIC-8_3.9x4.9mm_P1.27mm

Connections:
/5V_SENSE_TP_ONLY: J4.10, TP4.1 (1_1)
/+3V3_PI: C1.1, C2.1, J1.1, J1.17, J4.1, J6.1, R1.1, R2.1, R7.1, R11.1, R12.1, TP5.1 (1_1), U1.1 (VCC), U2.1 (VCC)
/+5V_PI: C3.1, C4.1, D1.1 (K), J1.2, J1.4, J5.1, TP6.1 (1_1)
/AMP_SD: J1.16, J4.9
/BASE_C0TX_N: J3.3, U2.6 (Z)
/BASE_C0TX_P: J3.2, U2.5 (Y)
/BASE_C3TX_N: J3.4, R4.2, U2.7 (B)
/BASE_C3TX_P: J3.5, R4.1, U2.8 (A)
/BASE_RX: J1.29, U2.2 (R)
/BASE_TX: J1.7, R2.2, U2.3 (D)
/BCLK: J1.12, J4.4
/BTN_GPIO12: C5.1, J1.32, R8.2
/BTN_SENSE: J6.5, R7.2, R8.1
/FAN_EN: J1.18, R5.1
/FAN_GATE: Q1.1 (G), R5.2, R6.1
/FAN_SW: D1.2 (A), J5.2, Q1.3 (D)
/GND: C1.2, C2.2, C3.2, C4.2, C5.2, J1.6, J1.9, J1.14, J1.20, J1.25, J1.30, J1.34, J1.39, J2.1, J3.1, J4.3, J4.5, J6.4, Q1.2 (S), R6.2, R10.2, TP3.1 (1_1), U1.4 (GND), U2.4 (GND)
/HEAD_C0TX_N: J2.3, U1.6 (Z)
/HEAD_C0TX_P: J2.2, U1.5 (Y)
/HEAD_C2TX_N: J2.4, R3.2, U1.7 (B)
/HEAD_C2TX_P: J2.5, R3.1, U1.8 (A)
/HEAD_RX: J1.10, U1.2 (R)
/HEAD_TX: J1.8, R1.2, U1.3 (D)
/I2C1_SCL: J1.5, TP2.1 (1_1)
/I2C1_SDA: J1.3, TP1.1 (1_1)
/I2C_GPIO_SCL: J1.37, J6.3, R12.2
/I2C_GPIO_SDA: J1.36, J6.2, R11.2
/LRCLK: J1.35, J4.2
/OFF_GPIO13: J1.33, R9.1
/PWR_OFF: J6.6, R9.2, R10.1
/SDI0: J1.38, J4.8
/SDI1: J1.15, J4.7
/SDO0: J1.40, J4.6

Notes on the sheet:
PI HEADER / D-073
HEAD RS-422 / UART0
BASE RS-422 / UART2
AUDIO / W26 SIGNALS ONLY
ENCLOSURE FAN / GPIO24
REAR SERVICE / W40 + W44
SERVICE / TEST PADS

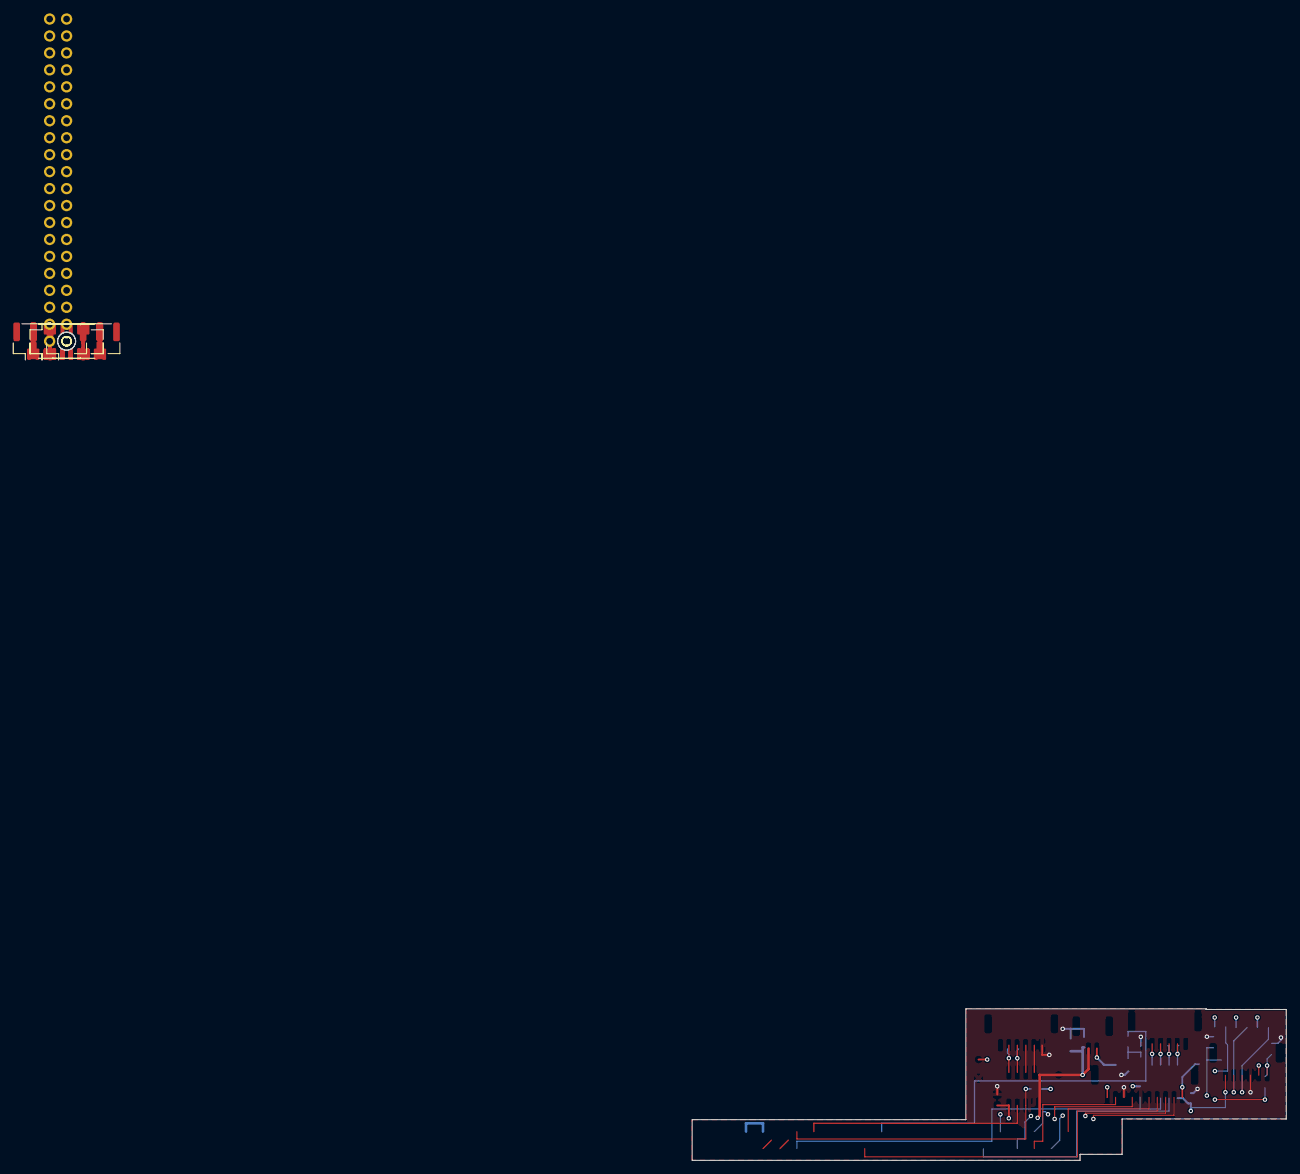
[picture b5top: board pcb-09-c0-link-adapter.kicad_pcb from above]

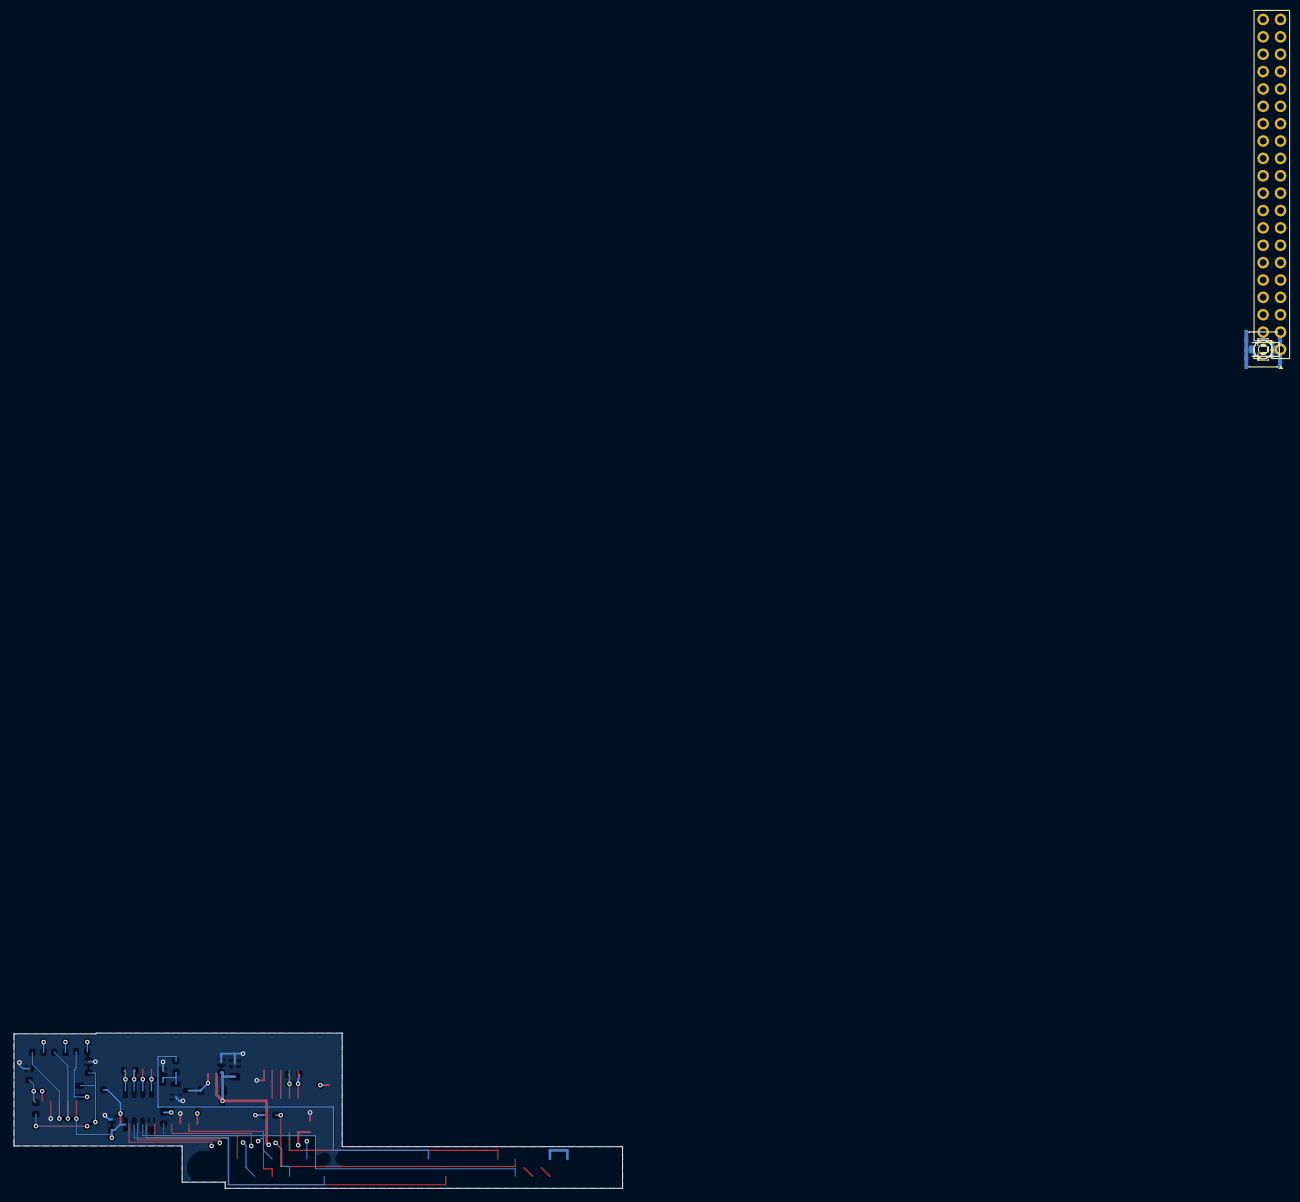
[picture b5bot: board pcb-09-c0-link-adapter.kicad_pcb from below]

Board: 4 copper layers, 89.0 x 22.7 mm, 35 parts (21 on the bottom side), 33 nets.

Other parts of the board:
H1, H2: MountingHole_2.7mm_M2.5

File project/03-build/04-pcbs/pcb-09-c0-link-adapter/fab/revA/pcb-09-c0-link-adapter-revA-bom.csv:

"Comment","Designator","Footprint","Quantity","MPN","Manufacturer","LCSC Part #"
"100n","C1,C2,C4","Capacitor_SMD:C_0603_1608Metric","3","","",""
"10u_10V","C3","Capacitor_SMD:C_0805_2012Metric","1","","",""
"1N5819HW","D1","Diode_SMD:D_SOD-123","1","1N5819HW-7-F","Diodes Inc.",""
"SSW-120-01-T-D","J1","Connector_PinSocket_2.54mm:PinSocket_2x20_P2.54mm_Vertical","1","SSW-120-01-T-D","Samtec",""
"J9-1_HEAD","J2","Connector_JST:JST_GH_SM06B-GHS-TB_1x06-1MP_P1.25mm_Horizontal","1","SM06B-GHS-TB(LF)(SN)","JST",""
"J9-2_BASE","J3","Connector_JST:JST_GH_BM06B-GHS-TBT_1x06-1MP_P1.25mm_Vertical","1","BM06B-GHS-TBT(LF)(SN)(N)","JST",""
"J9-3_AUDIO_W26","J4","Connector_JST:JST_GH_BM10B-GHS-TBT_1x10-1MP_P1.25mm_Vertical","1","BM10B-GHS-TBT(LF)(SN)(N)","JST",""
"J9-4_FAN","J5","Connector_JST:JST_GH_BM02B-GHS-TBT_1x02-1MP_P1.25mm_Vertical","1","BM02B-GHS-TBT(LF)(SN)(N)","JST",""
"AO3400A","Q1","Package_TO_SOT_SMD:SOT-23","1","AO3400A","Alpha & Omega",""
"4.7k","R1,R2","Resistor_SMD:R_0603_1608Metric","2","","",""
"120","R3,R4","Resistor_SMD:R_0603_1608Metric","2","","",""
"100","R5","Resistor_SMD:R_0603_1608Metric","1","","",""
"100k","R6","Resistor_SMD:R_0603_1608Metric","1","","",""
"THVD1451DR","U1,U2","Package_SO:SOIC-8_3.9x4.9mm_P1.27mm","2","THVD1451DR","Texas Instruments",""
